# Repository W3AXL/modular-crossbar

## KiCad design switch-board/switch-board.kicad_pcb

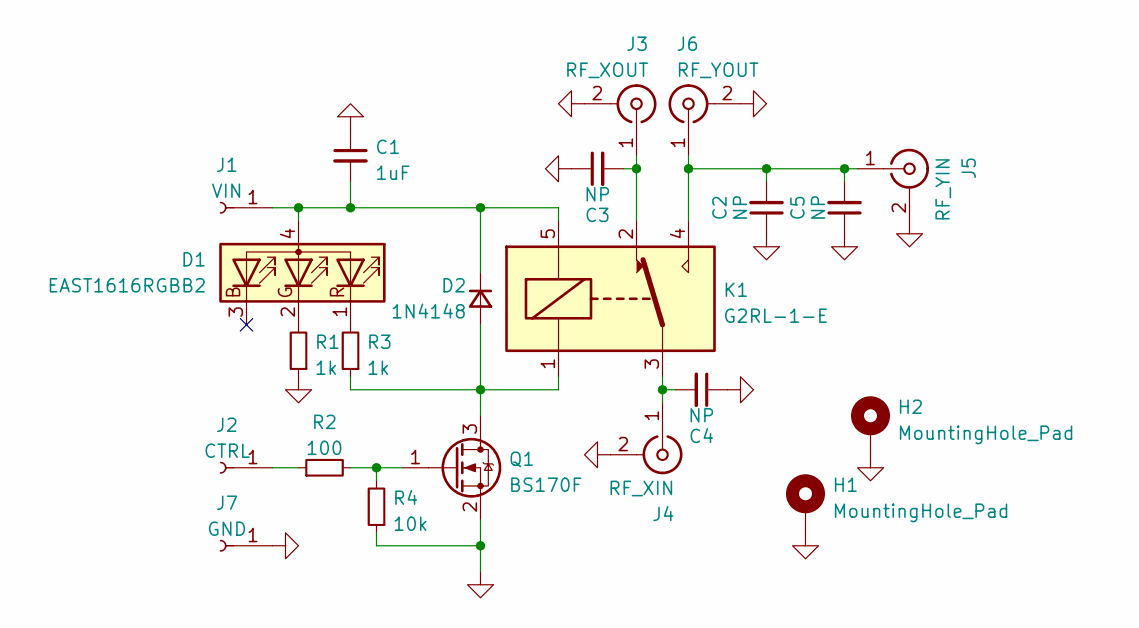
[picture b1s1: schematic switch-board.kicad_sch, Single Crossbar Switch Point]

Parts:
C1: 1uF; C_0805_2012Metric_Pad1.18x1.45mm_HandSolder
C2, C3, C4, C5: NP; C_1812_4532Metric_Pad1.57x3.40mm_HandSolder
D1: EAST1616RGBB2; LED_SMD_1616_RGBA
D2: 1N4148; D_SOD-323_HandSoldering
H1, H2: MountingHole_Pad; MountingHole_4.3mm_M4_Pad
J1: VIN; TestPoint_Pad_1.5x1.5mm
J2: CTRL; TestPoint_Pad_1.5x1.5mm
J3: RF_XOUT; Coax_Edge_2.54_1.27
J4: RF_XIN; Coax_Edge_2.54_1.27
J5: RF_YIN; Coax_Edge_2.54_1.27
J6: RF_YOUT; Coax_Edge_2.54_1.27
J7: GND; TestPoint_Pad_1.5x1.5mm
K1: G2RL-1-E; G2RL-1E
Q1: BS170F; SOT-23
R1, R3: 1k; R_0805_2012Metric_Pad1.20x1.40mm_HandSolder
R2: 100; R_0805_2012Metric_Pad1.20x1.40mm_HandSolder
R4: 10k; R_0805_2012Metric_Pad1.20x1.40mm_HandSolder

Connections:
GND: C1.1, C2.1, C3.1, C4.1, C5.1, H1.1, H2.1, J3.2 (Ext), J4.2 (Ext), J5.2 (Ext), J6.2 (Ext), J7.1, Q1.2 (S), R1.1, R4.1
unnamed: C1.2, D1.4 (A), D2.1 (K), J1.1, K1.5
unnamed: C3.2, J3.1 (In), K1.2
unnamed: C4.2, J4.1 (In), K1.3
unnamed: D1.1 (RK), R3.2
unnamed: D1.2 (GK), R1.2
unnamed: D2.2 (A), K1.1, Q1.3 (D), R3.1
unnamed: J2.1, R2.1
unnamed: C2.2, C5.2, J5.1 (In), J6.1 (In), K1.4
unnamed: Q1.1 (G), R2.2, R4.2

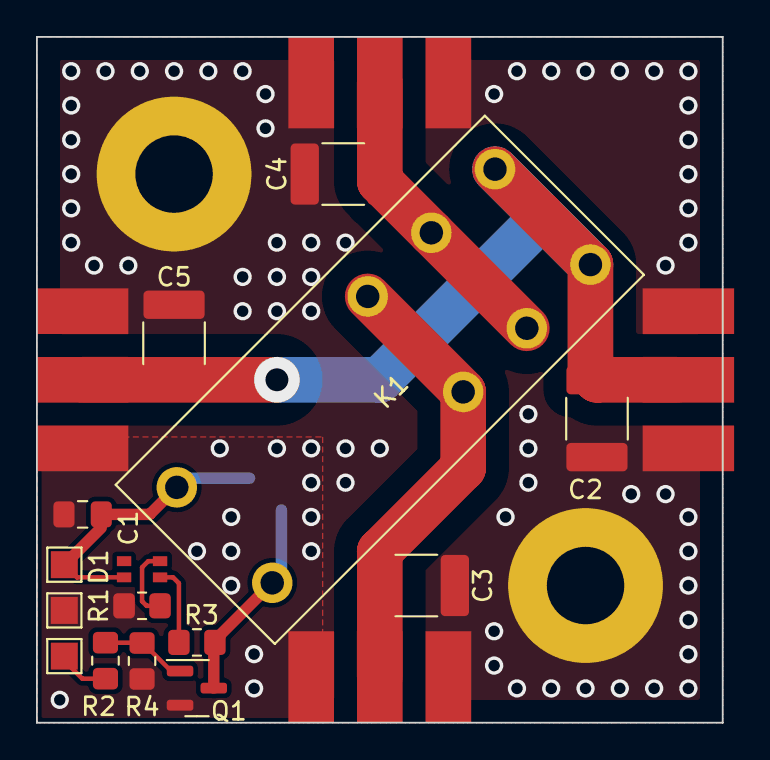
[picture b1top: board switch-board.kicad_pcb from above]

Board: 2 copper layers, 38.1 x 38.1 mm, 22 parts (1 on the bottom side), 10 nets.

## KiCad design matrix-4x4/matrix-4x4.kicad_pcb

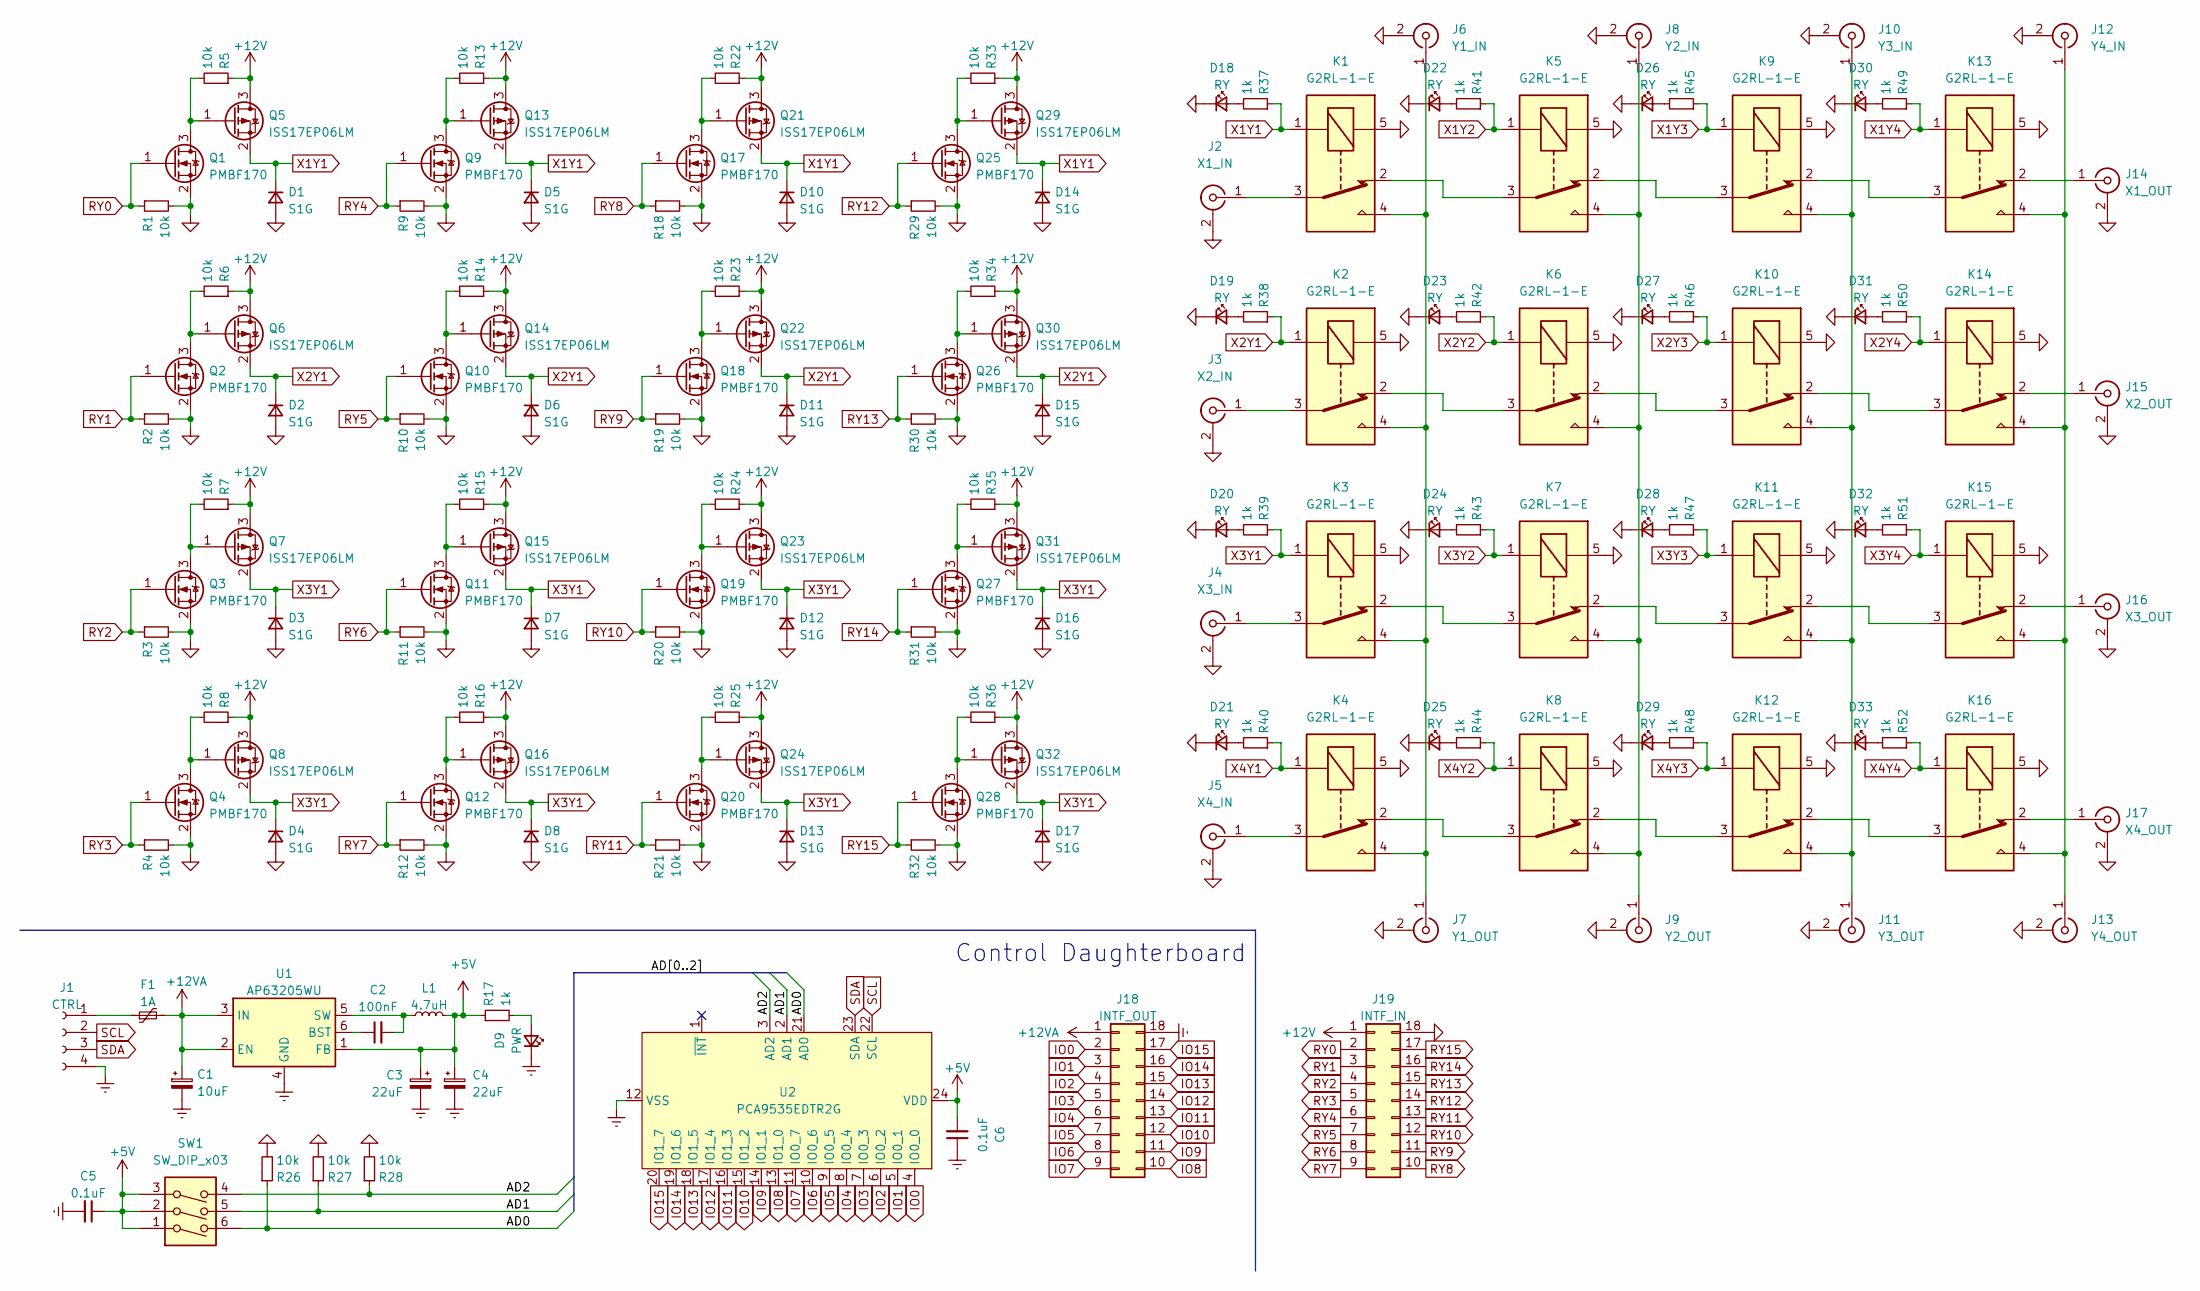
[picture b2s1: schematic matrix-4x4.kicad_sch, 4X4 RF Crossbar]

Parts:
C1: 10uF; CP_EIA-3528-15_AVX-H_Pad1.50x2.35mm_HandSolder
C2: 100nF; C_0805_2012Metric_Pad1.18x1.45mm_HandSolder
C3, C4: 22uF; CP_EIA-3528-15_AVX-H_Pad1.50x2.35mm_HandSolder
C5, C6: 0.1uF; C_0805_2012Metric_Pad1.18x1.45mm_HandSolder
D1, D2, D3, D4, D5, D6, D7, D8, D10, D11, D12, D13, D14, D15, D16, D17: S1G; D_SMA
D9: PWR; LED_0805_2012Metric_Pad1.15x1.40mm_HandSolder
D18, D19, D20, D21, D22, D23, D24, D25, D26, D27, D28, D29, D30, D31, D32, D33: RY; LED_0805_2012Metric_Pad1.15x1.40mm_HandSolder
F1: 1A; Fuse_1206_3216Metric_Pad1.42x1.75mm_HandSolder
J1: CTRL; PinHeader_1x04_P2.54mm_Vertical
J2: X1_IN; Coax_Edge_2.54_1.27
J3: X2_IN; Coax_Edge_2.54_1.27
J4: X3_IN; Coax_Edge_2.54_1.27
J5: X4_IN; Coax_Edge_2.54_1.27
J6: Y1_IN; Coax_Edge_2.54_1.27
J7: Y1_OUT; Coax_Edge_2.54_1.27
J8: Y2_IN; Coax_Edge_2.54_1.27
J9: Y2_OUT; Coax_Edge_2.54_1.27
J10: Y3_IN; Coax_Edge_2.54_1.27
J11: Y3_OUT; Coax_Edge_2.54_1.27
J12: Y4_IN; Coax_Edge_2.54_1.27
J13: Y4_OUT; Coax_Edge_2.54_1.27
J14: X1_OUT; Coax_Edge_2.54_1.27
J15: X2_OUT; Coax_Edge_2.54_1.27
J16: X3_OUT; Coax_Edge_2.54_1.27
J17: X4_OUT; Coax_Edge_2.54_1.27
J18: INTF_OUT; PinHeader_2x09_P2.00mm_Vertical
J19: INTF_IN; PinSocket_2x09_P2.00mm_Vertical
K1, K2, K3, K4, K5, K6, K7, K8, K9, K10, K11, K12, K13, K14, K15, K16: G2RL-1-E; G2RL-1E
L1: 4.7uH; L_Taiyo-Yuden_NR-30xx_HandSoldering
Q1, Q2, Q3, Q4, Q9, Q10, Q11, Q12, Q17, Q18, Q19, Q20, Q25, Q26, Q27, Q28: PMBF170; SOT-23_Handsoldering
Q5, Q6, Q7, Q8, Q13, Q14, Q15, Q16, Q21, Q22, Q23, Q24, Q29, Q30, Q31, Q32: ISS17EP06LM; SOT-23_Handsoldering
R1, R2, R3, R4, R5, R6, R7, R8, R9, R10, R11, R12, R13, R14, R15, R16, R18, R19, R20, R21, R22, R23, R24, R25, R26, R27, R28, R29, R30, R31, R32, R33, R34, R35, R36: 10k; R_0805_2012Metric_Pad1.20x1.40mm_HandSolder
R17, R37, R38, R39, R40, R41, R42, R43, R44, R45, R46, R47, R48, R49, R50, R51, R52: 1k; R_0805_2012Metric_Pad1.20x1.40mm_HandSolder
SW1: SW_DIP_x03; SW_DIP_SPSTx03_Slide_6.7x9.18mm_W7.62mm_P2.54mm_LowProfile
U1: AP63205WU; TSOT-23-6
U2: PCA9535EDTR2G; SOIC-24W_7.5x15.4mm_P1.27mm

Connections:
+5V: C3.1, C4.1, C5.1, C6.2, L1.2, R17.1, SW1.1, SW1.2, SW1.3, U1.1 (FB), U2.24 (VDD)
+12V: J19.1, Q5.3 (D), Q6.3 (D), Q7.3 (D), Q8.3 (D), Q13.3 (D), Q14.3 (D), Q15.3 (D), Q16.3 (D), Q21.3 (D), Q22.3 (D), Q23.3 (D), Q24.3 (D), Q29.3 (D), Q30.3 (D), Q31.3 (D), Q32.3 (D), R5.1, R6.1, R7.1, R8.1, R13.1, R14.1, R15.1, R16.1, R22.1, R23.1, R24.1, R25.1, R33.1, R34.1, R35.1, R36.1
+12VA: C1.1, F1.2, J18.1, U1.2 (EN), U1.3 (IN)
/AD0: R26.1, SW1.6, U2.21 (AD0)
/AD1: R27.1, SW1.5, U2.2 (AD1)
/AD2: R28.1, SW1.4, U2.3 (AD2)
GND: D1.2 (A), D2.2 (A), D3.2 (A), D4.2 (A), D5.2 (A), D6.2 (A), D7.2 (A), D8.2 (A), D10.2 (A), D11.2 (A), D12.2 (A), D13.2 (A), D14.2 (A), D15.2 (A), D16.2 (A), D17.2 (A), D18.1 (K), D19.1 (K), D20.1 (K), D21.1 (K), D22.1 (K), D23.1 (K), D24.1 (K), D25.1 (K), D26.1 (K), D27.1 (K), D28.1 (K), D29.1 (K), D30.1 (K), D31.1 (K), D32.1 (K), D33.1 (K), J2.2 (Ext), J3.2 (Ext), J4.2 (Ext), J5.2 (Ext), J6.2 (Ext), J7.2 (Ext), J8.2 (Ext), J9.2 (Ext), J10.2 (Ext), J11.2 (Ext), J12.2 (Ext), J13.2 (Ext), J14.2 (Ext), J15.2 (Ext), J16.2 (Ext), J17.2 (Ext), J19.18, K1.5, K2.5, K3.5, K4.5, K5.5, K6.5, K7.5, K8.5, K9.5, K10.5, K11.5, K12.5, K13.5, K14.5, K15.5, K16.5, Q1.2 (S), Q2.2 (S), Q3.2 (S), Q4.2 (S), Q9.2 (S), Q10.2 (S), Q11.2 (S), Q12.2 (S), Q17.2 (S), Q18.2 (S), Q19.2 (S), Q20.2 (S), Q25.2 (S), Q26.2 (S), Q27.2 (S), Q28.2 (S), R1.2, R2.2, R3.2, R4.2, R9.2, R10.2, R11.2, R12.2, R18.2, R19.2, R20.2, R21.2, R26.2, R27.2, R28.2, R29.2, R30.2, R31.2, R32.2
GNDREF: C1.2, C3.2, C4.2, C5.2, C6.1, D9.1 (K), J1.4, J18.18, U1.4 (GND), U2.12 (VSS)
IO0: J18.2, U2.4 (IO0_0)
IO1: J18.3, U2.5 (IO0_1)
IO2: J18.4, U2.6 (IO0_2)
IO3: J18.5, U2.7 (IO0_3)
IO4: J18.6, U2.8 (IO0_4)
IO5: J18.7, U2.9 (IO0_5)
IO6: J18.8, U2.10 (IO0_6)
IO7: J18.9, U2.11 (IO0_7)
IO8: J18.10, U2.13 (IO1_0)
IO9: J18.11, U2.14 (IO1_1)
IO10: J18.12, U2.15 (IO1_2)
IO11: J18.13, U2.16 (IO1_3)
IO12: J18.14, U2.17 (IO1_4)
IO13: J18.15, U2.18 (IO1_5)
IO14: J18.16, U2.19 (IO1_6)
IO15: J18.17, U2.20 (IO1_7)
unnamed: C2.1, U1.6 (BST)
unnamed: C2.2, L1.1, U1.5 (SW)
unnamed: D9.2 (A), R17.2
unnamed: D18.2 (A), R37.2
unnamed: D19.2 (A), R38.2
unnamed: D20.2 (A), R39.2
unnamed: D21.2 (A), R40.2
unnamed: D22.2 (A), R41.2
unnamed: D23.2 (A), R42.2
unnamed: D24.2 (A), R43.2
unnamed: D25.2 (A), R44.2
unnamed: D26.2 (A), R45.2
unnamed: D27.2 (A), R46.2
unnamed: D28.2 (A), R47.2
unnamed: D29.2 (A), R48.2
unnamed: D30.2 (A), R49.2
unnamed: D31.2 (A), R50.2
unnamed: D32.2 (A), R51.2
unnamed: D33.2 (A), R52.2
unnamed: F1.1, J1.1
unnamed: J2.1 (In), K1.3
unnamed: J3.1 (In), K2.3
unnamed: J4.1 (In), K3.3
unnamed: J5.1 (In), K4.3
unnamed: J6.1 (In), J7.1 (In), K1.4, K2.4, K3.4, K4.4
unnamed: J8.1 (In), J9.1 (In), K5.4, K6.4, K7.4, K8.4
unnamed: J10.1 (In), J11.1 (In), K9.4, K10.4, K11.4, K12.4
unnamed: J12.1 (In), J13.1 (In), K13.4, K14.4, K15.4, K16.4
unnamed: J14.1 (In), K13.2
unnamed: J15.1 (In), K14.2
unnamed: J16.1 (In), K15.2
unnamed: J17.1 (In), K16.2
unnamed: K2.2, K6.3
unnamed: K3.2, K7.3
unnamed: K4.2, K8.3
unnamed: K5.2, K9.3
unnamed: K1.2, K5.3
unnamed: K10.2, K14.3
unnamed: K6.2, K10.3
unnamed: K11.2, K15.3
unnamed: K7.2, K11.3
unnamed: K12.2, K16.3
unnamed: K8.2, K12.3
unnamed: K9.2, K13.3
unnamed: Q1.3 (D), Q5.1 (G), R5.2
unnamed: Q2.3 (D), Q6.1 (G), R6.2
unnamed: Q3.3 (D), Q7.1 (G), R7.2
unnamed: Q4.3 (D), Q8.1 (G), R8.2
unnamed: Q10.3 (D), Q14.1 (G), R14.2
unnamed: Q11.3 (D), Q15.1 (G), R15.2
unnamed: Q12.3 (D), Q16.1 (G), R16.2
unnamed: Q9.3 (D), Q13.1 (G), R13.2
unnamed: Q17.3 (D), Q21.1 (G), R22.2
unnamed: Q18.3 (D), Q22.1 (G), R23.2
unnamed: Q19.3 (D), Q23.1 (G), R24.2
unnamed: Q20.3 (D), Q24.1 (G), R25.2
unnamed: Q25.3 (D), Q29.1 (G), R33.2
unnamed: Q26.3 (D), Q30.1 (G), R34.2
unnamed: Q27.3 (D), Q31.1 (G), R35.2
unnamed: Q28.3 (D), Q32.1 (G), R36.2
RY0: J19.2, Q1.1 (G), R1.1
RY1: J19.3, Q2.1 (G), R2.1
RY2: J19.4, Q3.1 (G), R3.1
RY3: J19.5, Q4.1 (G), R4.1
RY4: J19.6, Q9.1 (G), R9.1
RY5: J19.7, Q10.1 (G), R10.1
RY6: J19.8, Q11.1 (G), R11.1
RY7: J19.9, Q12.1 (G), R12.1
RY8: J19.10, Q17.1 (G), R18.1
RY9: J19.11, Q18.1 (G), R19.1
RY10: J19.12, Q19.1 (G), R20.1
RY11: J19.13, Q20.1 (G), R21.1
RY12: J19.14, Q25.1 (G), R29.1
RY13: J19.15, Q26.1 (G), R30.1
RY14: J19.16, Q27.1 (G), R31.1
RY15: J19.17, Q28.1 (G), R32.1
SCL: J1.2, U2.22 (SCL)
SDA: J1.3, U2.23 (SDA)
X1Y1: D1.1 (K), D5.1 (K), D10.1 (K), D14.1 (K), K1.1, Q5.2 (S), Q13.2 (S), Q21.2 (S), Q29.2 (S), R37.1
X1Y2: K5.1, R41.1
X1Y3: K9.1, R45.1
X1Y4: K13.1, R49.1
X2Y1: D2.1 (K), D6.1 (K), D11.1 (K), D15.1 (K), K2.1, Q6.2 (S), Q14.2 (S), Q22.2 (S), Q30.2 (S), R38.1
X2Y2: K6.1, R42.1
X2Y3: K10.1, R46.1
X2Y4: K14.1, R50.1
X3Y1: D3.1 (K), D4.1 (K), D7.1 (K), D8.1 (K), D12.1 (K), D13.1 (K), D16.1 (K), D17.1 (K), K3.1, Q7.2 (S), Q8.2 (S), Q15.2 (S), Q16.2 (S), Q23.2 (S), Q24.2 (S), Q31.2 (S), Q32.2 (S), R39.1
X3Y2: K7.1, R43.1
X3Y3: K11.1, R47.1
X3Y4: K15.1, R51.1
X4Y1: K4.1, R40.1
X4Y2: K8.1, R44.1
X4Y3: K12.1, R48.1
X4Y4: K16.1, R52.1

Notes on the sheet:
Control Daughterboard

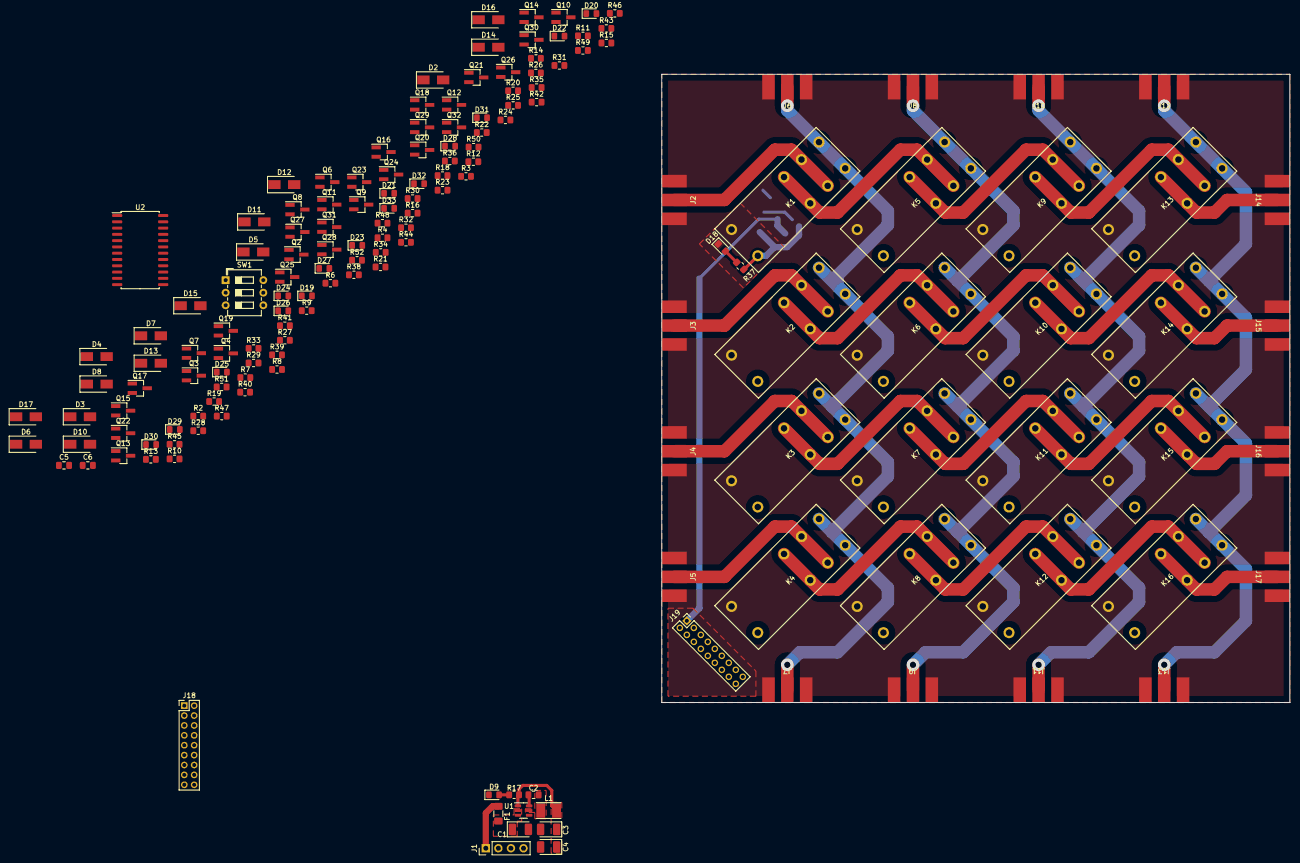
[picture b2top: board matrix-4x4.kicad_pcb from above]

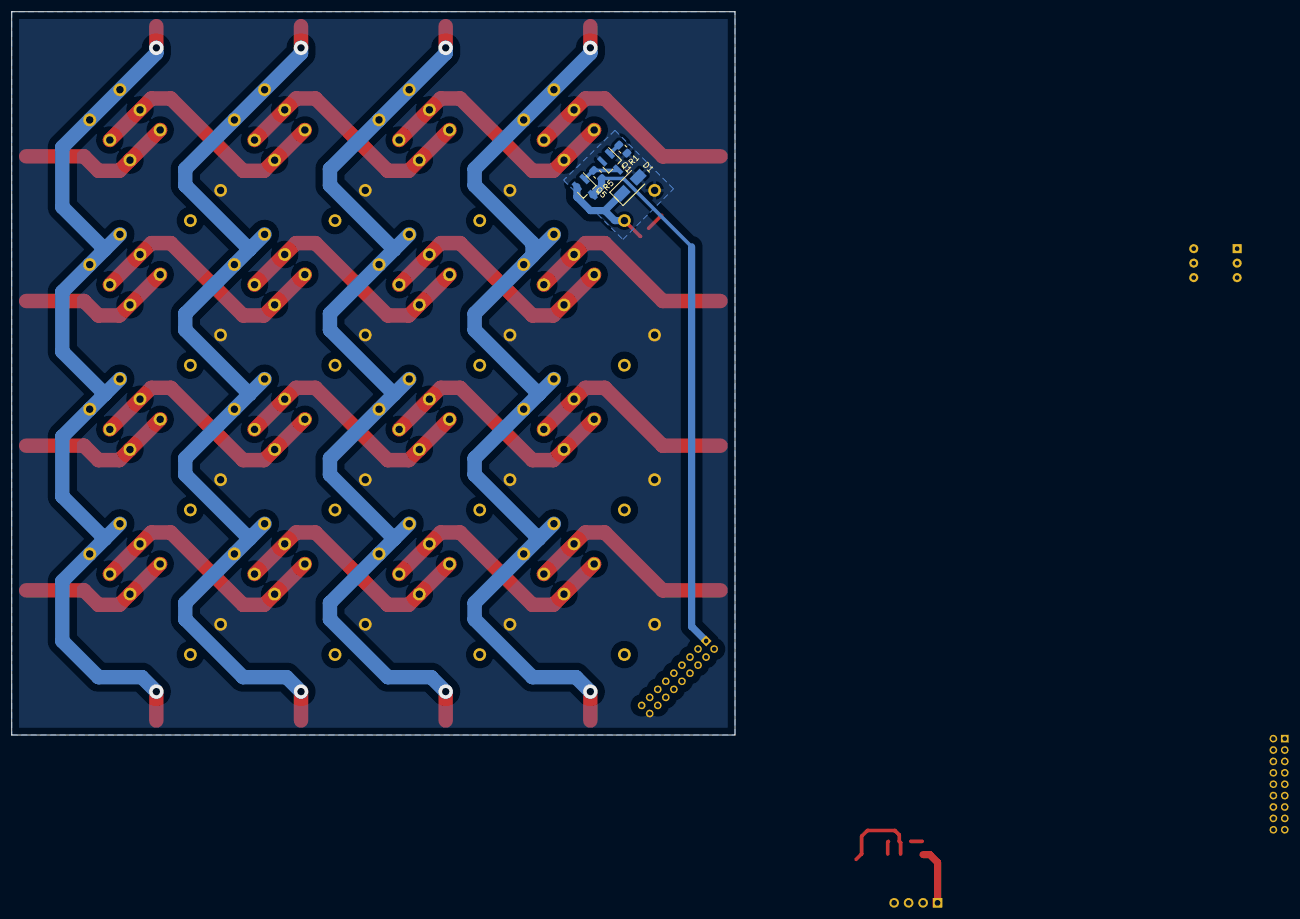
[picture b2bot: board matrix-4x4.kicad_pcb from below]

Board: 2 copper layers, 127.0 x 127.0 mm, 163 parts (5 on the bottom side), 118 nets.

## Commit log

2022-09-08 initial schematic work for relay board
2022-09-09 finalized rev A PCB
2022-09-12 started work on 4x4 matrix board
2022-09-13 finalized single-point switch design, more work on 4x4 matrix
